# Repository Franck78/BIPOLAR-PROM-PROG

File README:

BIPOLAR PROM PROGRAMMER

Another one in the arena !

This one is based on the Atmega to repeat easily programming a PROM.

It reads the source from a master PROM
It writes what is memory to a virgin PROM

Values can be modified on the fly if needed. That is similar to
the 'manual' programmers found everywhere.

A default PROM file is used when 'Read' is pressed and nothing is in the socket.
The goal of this project was programming a dozen of PROMS, so it makes sense for me
to have that default loaded.

TODO: use the internal eeprom of the mega to store/retrieve PROM files. 
TODO: use the serial port to send files (remember entering 32 values is not really
time consumming, so this is luxury.

I'm using KiCad 5. It works for me until I upgrade my old laptop. Don't send request
about version.

The code is occupying 85% of the AtMega88. What is code consumming is
the human interface ! Moving to atMega328 is possible.
TODO: remove DigitalRead DigitalWrite functions (code consumming I think)

version 1.0 of the pcb was really botched to work. Version v1.1 fixed all that
but I made a mistake with the G6K relay footprint. In this repository, this is
fixed.
But I still have 4 usable PCB from JLCPCB. Pin 1 and 8 of each relay need to be
swapped. It can be done by soldering the relay on the other side. I choose to
put them on the correct side and inserted insulation on the two pins then solder
correctly.

Another thing is the ZIF socket. AliExpress 3M Textool is shit reproduction.
I ordered Aries reproduction, much better but pin space is 'wide'. But they
can be used. They can also be opened (a good hammer and strong pin) to 
reinsert each contact to get the narrow version.

HOW TO used

Insert the PROM to copy in the 'Read' socket, press 'R' button

The CRC32 is displayed until another key is pressed.
If all zero is read, then the default PROM file is used. 
This is signaled by a double beep.

Use + / - to display each address and content.
Press V to edit a value (with + / -). Display starts
blinking.
Press V again to accept the updated value.

When everything is OK, insert a virgin PROM and press 'W'
Program will fuse bit 0 on each 32 position, then bit 1
then ... This limits the relays actuating.

Read of the 'Write' socket is done for comparison. When
green LED lits, it is a success.
If not, retry. Only failed bits will be refused.

The serial port reports outputs what the programmer is doing.
Is is not required to have a terminal nut it helps.

I had in mind some flexibility for the current programming 
(the pulse). I did not explore possibilities of burning
other brand.
I have tested the programmer with

N82S23AN (K8608) from Signetics.
with minor modification and new software
TBP18S030N

I have 4 spare PCB to sell (instead of asking 5 new ones to JLPCB).
I'm not doing that for the money of course but avoid filling my bin.

About the PCB
I wanted sockets and button covered properly in a box. This why
all 'big' components are on the bottom side. 
Need to make a box now ;)

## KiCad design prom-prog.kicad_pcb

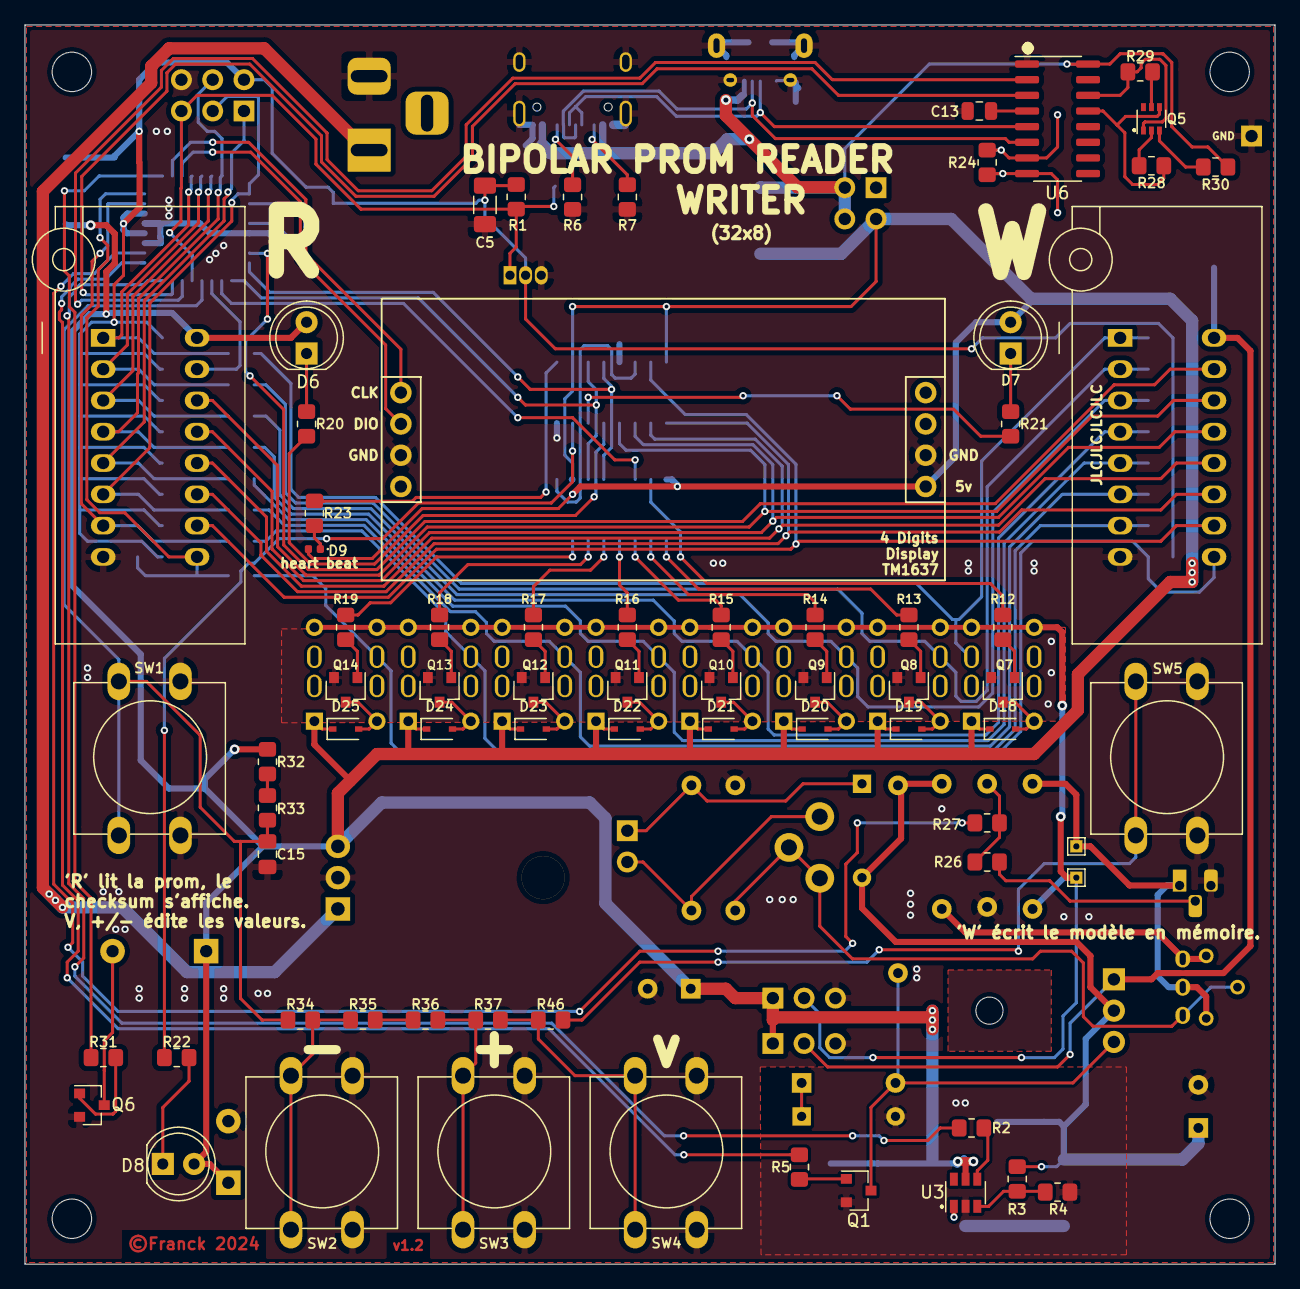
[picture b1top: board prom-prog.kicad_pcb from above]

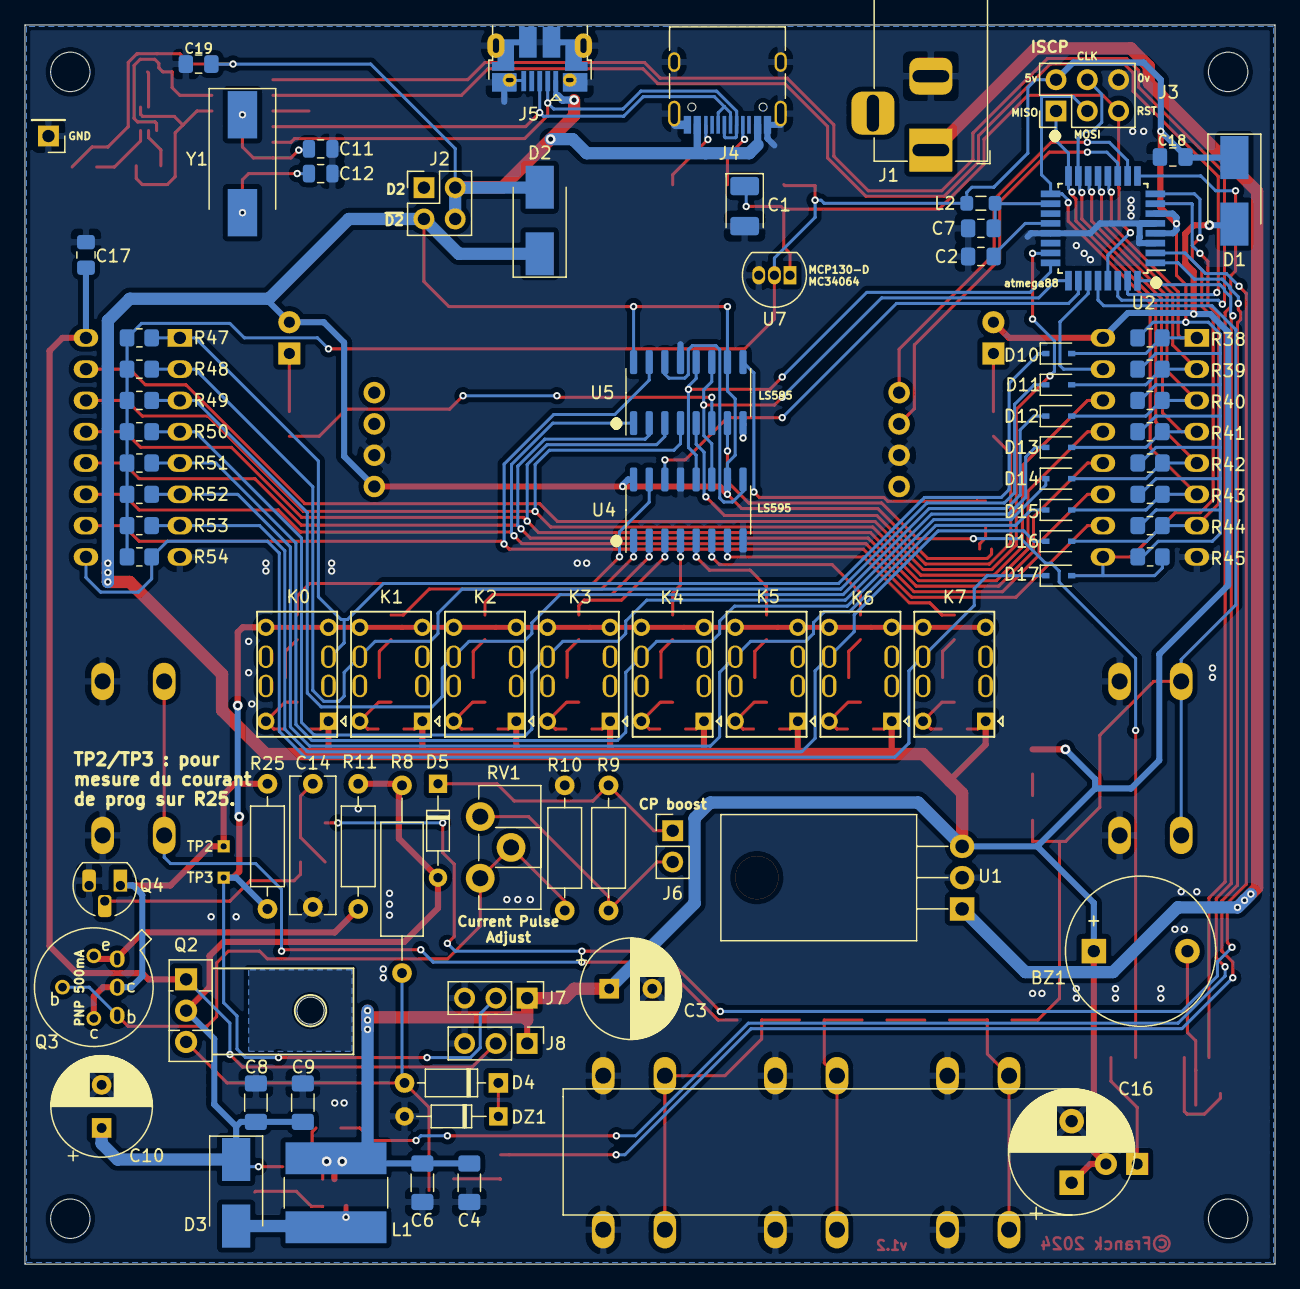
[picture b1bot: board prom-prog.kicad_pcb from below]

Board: 2 copper layers, 101.5 x 100.6 mm, 157 parts (81 on the bottom side), 112 nets.

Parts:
BZ1: Buzzer; Buzzer_12x9.5RM7.6
C1: 1µ/50v; CP_EIA-3528-21_Kemet-B_Pad1.50x2.35mm_HandSolder
C2, C7, C15, C17, C18, C19: 10n; C_0805_2012Metric_Pad1.18x1.45mm_HandSolder
C3: 100µ/25v; CP_Radial_D8.0mm_P3.50mm
C4, C6, C8, C9: 22µ/35v; C_1206_3216Metric_Pad1.33x1.80mm_HandSolder
C5: 100µ/10v; C_1206_3216Metric_Pad1.33x1.80mm_HandSolder
C10: 470/16v; CP_Radial_D8.0mm_P3.50mm
C11, C12: 33p; C_0805_2012Metric
C13: 100n; C_0805_2012Metric
C14: 8n2; C_Rect_L11.0mm_W3.5mm_P10.00mm_MKT
C16: 3300µ/10v; CP_Radial_D10.0mm_P5.00mm
D1, D2, D3: SS34; D_SMB_Handsoldering
D4: 1n4004; D_DO-35_SOD27_P7.62mm_Horizontal
D5: 1n4148; D_DO-34_SOD68_P7.62mm_Horizontal
D6, D7, D8: LED; LED_D5.0mm
D9: LED; LED_0402_1005Metric
D10, D11, D12, D13, D14, D15, D16, D17: 1n4148; D_SOD-323
D18, D19, D20, D21, D22, D23, D24, D25: BAS316; D_SOD-323
DG1: ali module; 4DigitSerial
DZ1: 10v; D_DO-34_SOD68_P7.62mm_Horizontal
H1, H2, H3, H4: MountingHole; MountingHole_3.2mm_M3
H5: MountingHole; MountingHole_2.2mm_M2_DIN965
IC1, IC2: MMI6331; DIP_Socket-16_W4.3_W5.08_W7.62_W10.16_W10.9_3M_216-3340-00-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
J1: Barrel_Jack; BarrelJack_Horizontal
J2: Conn_02x02_Odd_Even; PinHeader_2x02_P2.54mm_Vertical
J3: Conn_02x03_Odd_Even; PinHeader_2x03_P2.54mm_Vertical
J4: USB_C_Receptacle_USB2.0; USB_C_Receptacle_HRO_TYPE-C-31-M-12
J5: USB_B_Micro; USB_Micro-B_AliExpress
J6: 50ma / 60ma; PinHeader_1x02_P2.54mm_Vertical
J7, J8: Power; PinHeader_1x03_P2.54mm_Vertical
K0, K1, K2, K3, K4, K5, K6, K7: G6K-2; G6K-2P-YZ
L1: 10µH; L_Bourns-SRN8040_8x8.15mm
L2: 10µH; L_0805_2012Metric_Pad1.05x1.20mm_HandSolder
Q1, Q6, Q7, Q8, Q9, Q10, Q11, Q12, Q13, Q14: BSS138; SOT-23
Q2: BD139; TO-126-3_Vertical
Q3: BC160; TO-39-3
Q4: BC237; TO-92_HandSolder
Q5: DUAL_2222; SOT-363_SC-70-6
R1, R5, R23, R30, R32, R33, R37: 1k; R_0805_2012Metric_Pad1.20x1.40mm_HandSolder
R2, R31: 220; R_0805_2012Metric_Pad1.20x1.40mm_HandSolder
R3, R46: 3k3; R_0805_2012Metric_Pad1.20x1.40mm_HandSolder
R4: 130; R_0805_2012Metric_Pad1.20x1.40mm_HandSolder
R6, R7: 5k1; R_0805_2012Metric_Pad1.20x1.40mm_HandSolder
R8: 270; R_Axial_DIN0309_L9.0mm_D3.2mm_P15.24mm_Horizontal
R9: 100; R_Axial_DIN0207_L6.3mm_D2.5mm_P10.16mm_Horizontal
R10: 10k; R_Axial_DIN0207_L6.3mm_D2.5mm_P10.16mm_Horizontal
R11: 18; R_Axial_DIN0207_L6.3mm_D2.5mm_P10.16mm_Horizontal
R12, R13, R14, R15, R16, R17, R18, R19, R26, R27, R38, R39, R40, R41, R42, R43, R44, R45, R47, R48, R49, R50, R51, R52, R53, R54: 10k; R_0805_2012Metric_Pad1.20x1.40mm_HandSolder
R20, R21, R22: 560; R_0805_2012Metric_Pad1.20x1.40mm_HandSolder
R24: 1M; R_0805_2012Metric_Pad1.20x1.40mm_HandSolder
R25: .1; R_Axial_DIN0207_L6.3mm_D2.5mm_P10.16mm_Horizontal
R28, R29: 10K; R_0805_2012Metric_Pad1.20x1.40mm_HandSolder
R34, R35, R36: 330; R_0805_2012Metric_Pad1.20x1.40mm_HandSolder
RV1: 2k2; Potentiometer_ACP_CA9-H2,5_Horizontal
SW1, SW2, SW3, SW4, SW5: SW_Push; SW_PUSH-12mm
TP1: TestPoint; PinHeader_1x01_P2.54mm_Vertical
TP2, TP3: TestPoint_Probe; TestPoint_THTPad_1.0x1.0mm_Drill0.5mm
U1: LM7805_TO220; TO-220-3_Horizontal_TabDown
U2: ATmega8A-AU; TQFP-32_7x7mm_P0.8mm
U3: MT3608; SOT-23-6
U4, U5: 74LS595; SOIC-16_3.9x9.9mm_P1.27mm
U6: CH340G; SOIC-16_3.9x9.9mm_P1.27mm
U7: MCP130-xxxDxTO; TO-92_Inline
Y1: 12Mhz; Crystal_SMD_EuroQuartz_MQ2-2Pin_7.0x5.0mm_HandSoldering

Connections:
+5V: BZ1.1, C3.1, C4.1, C6.1, C16.1, D1.2, D2.1, D6.2, D7.2, D8.2, D9.2, D18.1, D19.1, D20.1, D21.1, D22.1, D23.1, D24.1, D25.1, DG1.5, IC2.16, J2.3, J7.1, J8.1, K0.1, K1.1, K2.1, K3.1, K4.1, K5.1, K6.1, K7.1, L1.1, R32.1, U1.3, U3.5, U4.10, U4.16, U5.10, U5.16
/A0: IC1.10, IC2.10, U5.15
/A1: IC1.11, IC2.11, U5.1
/A2: IC1.12, IC2.12, U5.2
/A3: IC1.13, IC2.13, U5.3
/A4: IC1.14, IC2.14, U5.4
/BIT0: D10.1, IC1.1, K0.3, R47.2
/BIT1: D11.1, IC1.2, K1.6, R48.2
/BIT2: D12.1, IC1.3, K2.6, R49.2
/BIT3: D13.1, IC1.4, K3.6, R50.2
/BIT4: D14.1, IC1.5, K4.6, R51.2
/BIT5: D15.1, IC1.6, K5.6, R52.2
/BIT6: D16.1, IC1.7, K6.6, R53.2
/BIT7: D17.1, IC1.9, K7.6, R54.2
/BS0: Q7.1, R12.1
/BS1: Q8.1, R13.1
/BS2: Q9.1, R14.1
/BS3: Q10.1, R15.1
/BS4: Q11.1, R16.1
/BS5: Q12.1, R17.1
/BS6: Q13.1, R18.1
/BS7: Q14.1, R19.1
/Cprog: J7.2, K0.4, K0.5, K1.4, K1.5, K2.4, K2.5, K3.4, K3.5, K4.4, K4.5, K5.4, K5.5, K6.4, K6.5, K7.4, K7.5, R25.1, TP3.1
/Cprog_a: Q3.1, R11.2
/Cprog_b: Q3.3, Q4.1, R25.2, TP2.1
/D0: D10.2, IC2.1, R38.2, U2.12
/D1: D11.2, IC2.2, R39.2, U2.13
/D2: D12.2, IC2.3, R40.2, U2.14
/D3: D13.2, IC2.4, J3.4, R41.2, U2.15
/D4: D14.2, IC2.5, J3.1, R42.2, U2.16
/D5: D15.2, IC2.6, J3.3, R43.2, U2.17
/D6: D16.2, IC2.7, R44.2, U2.7
/D7: D17.2, IC2.9, R45.2, U2.8
/DG_CLK: DG1.1, U2.10
/DG_DIO: DG1.2, U2.11
/ISCP5v: C5.1, C18.2, D1.1, J3.2, L2.1, R1.1, R38.1, R39.1, R40.1, R41.1, R42.1, R43.1, R44.1, R45.1, R47.1, R48.1, R49.1, R50.1, R51.1, R52.1, R53.1, R54.1, U2.4, U2.6, U7.2
/RX: U2.30, U6.2
/TX: U2.31, U6.3
/UD+: J4.A6, J4.B6, J5.3, U6.5
/UD-: J4.A7, J4.B7, J5.2, U6.6
/VBUS: C19.2, D2.2, J2.2, J2.4, J4.A4, J4.A9, J4.B4, J4.B9, J5.1, R30.1, U6.16
/buckOn: R2.2, U2.32
/buttons: C15.1, R33.2, R34.1, SW1.1, U2.28
/buzzer: R31.2, U2.9
/fb: R3.2, R4.1, U3.3
/sw: D3.2, L1.2, U3.1
/vBuck: C8.1, C9.1, C10.1, D3.1, D5.2, Q2.2, R3.1, R8.1, R11.1
/vppBoost: R5.2, U2.1
/vppPulse: R27.2, U2.2
/~CSPROMR~: IC2.15, U2.27
/~CSPROMW~: IC1.15, U2.23
/~DTR: Q5.4, R28.2, U6.13
/~RST: C1.1, J3.5, R1.2, U2.29, U7.1
/~RTS: Q5.1, R29.2, U6.14
GND: C1.2, C2.2, C3.2, C4.2, C5.2, C6.2, C7.1, C8.2, C9.2, C10.2, C11.2, C12.2, C13.2, C14.1, C15.2, C16.2, C17.1, C18.1, C19.1, DG1.3, DG1.6, DZ1.2, IC1.8, IC2.8, J1.2, J3.6, J4.A1, J4.A12, J4.B1, J4.B12, J4.S1, J5.5, J5.6, J7.3, J8.3, Q1.2, Q4.3, Q6.2, Q7.2, Q8.2, Q9.2, Q10.2, Q11.2, Q12.2, Q13.2, Q14.2, R4.2, R6.1, R7.1, R10.1, SW1.2, SW2.2, SW3.2, SW4.2, SW5.2, TP1.1, U1.2, U2.3, U2.5, U2.21, U3.2, U4.8, U4.13, U5.8, U5.13, U6.1, U7.3
unnamed: BZ1.2, Q6.3
unnamed: C2.1, U2.20
unnamed: C7.2, L2.2, U2.18
unnamed: C11.1, R24.2, U6.7, Y1.1
unnamed: C12.1, R24.1, U6.8, Y1.2
unnamed: C13.1, U6.4
unnamed: C14.2, R26.2, R27.1
unnamed: D4.1, DZ1.1
unnamed: D4.2, Q1.3, Q2.3, R8.2
unnamed: D5.1, J6.1, R9.2
unnamed: D6.1, R20.1
unnamed: D7.1, R21.1
unnamed: D8.1, R22.1
unnamed: D9.1, R23.1
unnamed: D18.2, K0.8, Q7.3
unnamed: D19.2, K1.8, Q8.3
unnamed: D20.2, K2.8, Q9.3
unnamed: D21.2, K3.8, Q10.3
unnamed: D22.2, K4.8, Q11.3
unnamed: D23.2, K5.8, Q12.3
unnamed: D24.2, K6.8, Q13.3
unnamed: D25.2, K7.8, Q14.3
unnamed: J1.1, U1.1
unnamed: J4.A5, R6.2
unnamed: J4.B5, R7.2
unnamed: J6.2, R9.1, RV1.1
unnamed: Q1.1, R5.1
unnamed: Q3.2, R10.2, RV1.2, RV1.3
unnamed: Q4.2, R26.1
unnamed: Q5.2, R28.1
unnamed: Q5.3, R30.2
unnamed: Q5.5, R29.1
unnamed: Q6.1, R31.1
unnamed: R2.1, U3.4
unnamed: R12.2, U4.15
unnamed: R13.2, U4.1
unnamed: R14.2, U4.2
unnamed: R15.2, U4.3
unnamed: R16.2, U4.4
unnamed: R17.2, U4.5
unnamed: R18.2, U4.6
unnamed: R19.2, U4.7
unnamed: R20.2, U5.5
unnamed: R21.2, U5.6
unnamed: R22.2, U5.7
unnamed: R23.2, U5.9
unnamed: R32.2, R33.1
unnamed: R34.2, R35.1, SW2.1
unnamed: R35.2, R36.1
unnamed: R36.2, R37.1, SW3.1
unnamed: R37.2, R46.1, SW4.1
unnamed: R46.2, SW5.1
unnamed: U2.24, U4.12, U5.12
unnamed: U2.25, U4.11, U5.11
unnamed: U2.26, U4.14
unnamed: U4.9, U5.14
VPP: C17.2, IC1.16, J8.2, Q2.1

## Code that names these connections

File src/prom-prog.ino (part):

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 * 
 * PORTB 8 bits data bus from PromR and PromW
 * 
 * PC0 CSPROMW
 * PC1 HC595 latch rclk
 * PC2 HC595 serial clock
 * PC3 HC595 serial data
 * PC4 CSPROMR 
 * 
 * PC5 analogic buttons chain input
 * PC6 reset
 * PC7 nc
 * 
 * PD0 CH340 RX to USB
 * PD1 CH340 TX to USB
 * PD2 buckOn enable buck MT3608
 * PD3 vppBoost enable VPP or 5v
 * PD4 vppPulse pulseEnable
 * 
 * PD5 Buzzer
 * PD6_DG_CLK
 * PD7 DG_DIO (TM1637 4 digit display)
 *
 *
 * The burning generator hardware is based on Elektor september 1980 (french edition) prom programmer
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
#define tm1637_c      PD6
#define tm1637_d      PD7
#define buzzer        PD5
TM1637Display         Info(tm1637_c,tm1637_d);
boolean               blinkState;
boolean               canBlink, canBlink2;
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
// buckOn, vppBoost, vppPulse
// do not use digitalWrite
#define buckOn      4   /*(PD2)*/
#define vppNoBoost  8   /*(PD3)*/
#define vppQ4      16   /*(PD4)*/

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#define VPP0V_Q4closed  (0      + vppNoBoost + vppQ4) 
#define VPP5V_Q4open    (0                          )
#define VPP5V_Q4closed  (0                   + vppQ4)
#define VPP10V_Q4open   (buckOn                     )
#define VPP10V_Q4closed (buckOn              + vppQ4)


/*
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
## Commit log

2024-06-16 Add files via upload
    Initial load on github,
    maybe 'bordélique' ;)
2026-01-09 Added some code to test new PROM
    I have TPB18S030 to program and they are completely different algo.
    The hardware can be modified, the pulse procedure must be adapted to this change.
    Work in progress
2026-01-12 Good also for TBP18S030
    Need a small hardware change as well as a new programming method.
    The device is for one chip at a time with this pcb. It needs more work
    to have it for both but this is useless for now given the number of
    programming needed !
2026-01-12 fix comment about Elektor

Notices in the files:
prom-prog.kicad_pcb:
©Franck 2024
